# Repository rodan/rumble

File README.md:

# rumble

sandbox for geophone amplifiers

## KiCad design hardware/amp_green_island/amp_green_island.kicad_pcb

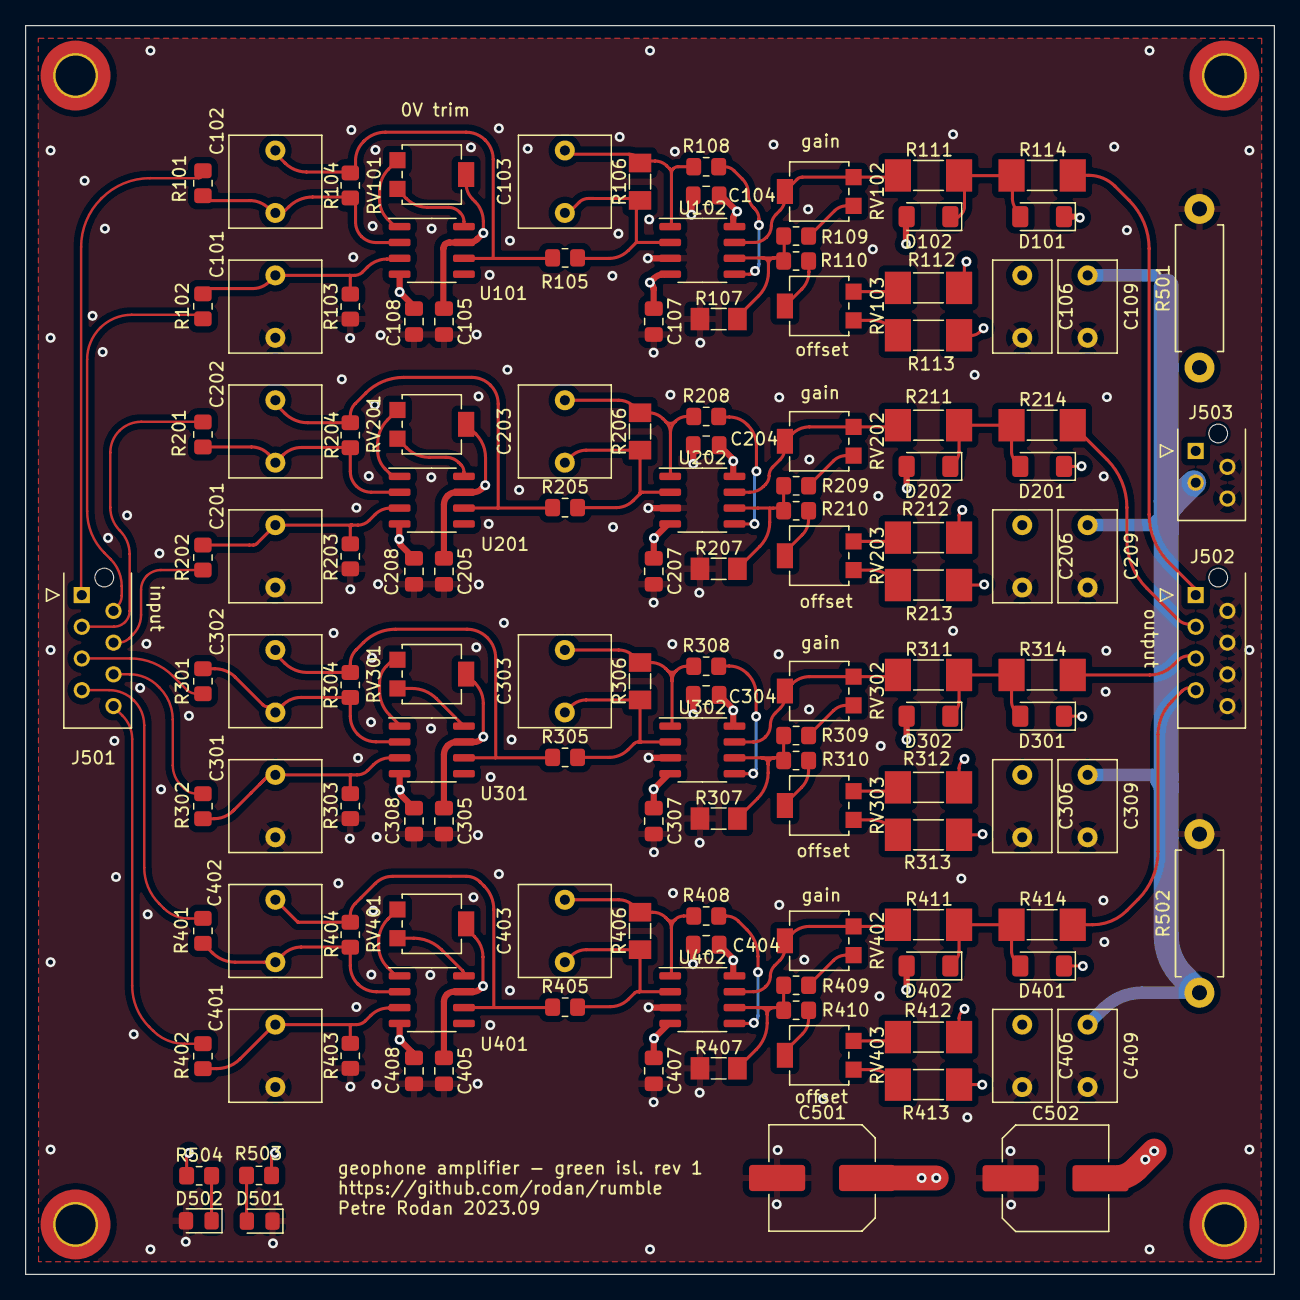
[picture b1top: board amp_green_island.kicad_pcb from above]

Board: 4 copper layers, 100.0 x 100.0 mm, 131 parts (0 on the bottom side), 77 nets.

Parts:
C101, C102, C103, C201, C202, C203, C301, C302, C303, C401, C402, C403: 1u; C_Rect_L7.2mm_W7.2mm_P5.00mm_FKS2_FKP2_MKS2_MKP2
C104, C105, C107, C108, C204, C205, C207, C208, C304, C305, C307, C308, C404, C405, C407, C408: 100n; C_0805_2012Metric_Pad1.18x1.45mm_HandSolder
C106, C109, C206, C209, C306, C309, C406, C409: 100n; C_Rect_L7.2mm_W4.5mm_P5.00mm_FKS2_FKP2_MKS2_MKP2
C501, C502: 220u; C_Elec_8x10.2
D101, D102, D201, D202, D301, D302, D401, D402: LL4148; D_MiniMELF
D501, D502: LED; LED_0805_2012Metric_Pad1.15x1.40mm_HandSolder
J501: input; TE_Micro-MaTch_215079-8_2x04_P1.27mm_Vertical
J502: output; TE_Micro-MaTch_215079-8_2x04_P1.27mm_Vertical
J503: Conn_01x04_Pin; TE_Micro-MaTch_215079-4_2x02_P1.27mm_Vertical
R101, R102, R201, R202, R301, R302, R401, R402: 10k; R_0805_2012Metric_Pad1.20x1.40mm_HandSolder
R103, R104, R203, R204, R303, R304, R403, R404, R503, R504: 100k; R_0805_2012Metric_Pad1.20x1.40mm_HandSolder
R105, R108, R205, R208, R305, R308, R405, R408: 1k; R_0805_2012Metric_Pad1.20x1.40mm_HandSolder
R106, R206, R306, R406: 200k; R_MiniMELF_MMA-0204
R107, R207, R307, R407: 3k3; R_MiniMELF_MMA-0204
R109, R209, R309, R409: 5k6; R_0805_2012Metric_Pad1.20x1.40mm_HandSolder
R110, R210, R310, R410: 82k; R_0805_2012Metric_Pad1.20x1.40mm_HandSolder
R111, R114, R211, R214, R311, R314, R411, R414: 470; R_MELF_MMB-0207
R112, R113, R212, R213, R312, R313, R412, R413: 33k; R_MELF_MMB-0207
R501, R502: 100; R_Axial_DIN0411_L9.9mm_D3.6mm_P12.70mm_Horizontal
RV101, RV201, RV301, RV401: 10k; Potentiometer_Bourns_3314G_Vertical
RV102, RV202, RV302, RV402: 50k; Potentiometer_Bourns_3314G_Vertical
RV103, RV203, RV303, RV403: 5k; Potentiometer_Bourns_3314G_Vertical
U101, U201, U301, U401: OP27; SO-8_3.9x4.9mm_P1.27mm
U102, U202, U302, U402: TL072; SO-8_3.9x4.9mm_P1.27mm

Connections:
+12V: C104.1, C105.1, C106.1, C204.1, C205.1, C206.1, C304.1, C305.1, C306.1, C404.1, C405.1, C406.1, C501.1, D101.1 (K), D201.1 (K), D301.1 (K), D401.1 (K), J503.1, R112.1, R212.1, R312.1, R412.1, R501.1, R503.1, RV101.2, RV201.2, RV301.2, RV401.2, U101.7 (V+), U102.8 (V+), U201.7 (V+), U202.8 (V+), U301.7 (V+), U302.8 (V+), U401.7 (V+), U402.8 (V+)
-12V: C107.1, C108.1, C109.1, C207.1, C208.1, C209.1, C307.1, C308.1, C309.1, C407.1, C408.1, C409.1, C502.2, D102.2 (A), D202.2 (A), D302.2 (A), D402.2 (A), J503.3, R113.2, R213.2, R313.2, R413.2, R502.1, R504.1, U101.4 (V-), U102.4 (V-), U201.4 (V-), U202.4 (V-), U301.4 (V-), U302.4 (V-), U401.4 (V-), U402.4 (V-)
GND: C101.1, C104.2, C105.2, C106.2, C107.2, C108.2, C109.2, C201.1, C204.2, C205.2, C206.2, C207.2, C208.2, C209.2, C301.1, C304.2, C305.2, C306.2, C307.2, C308.2, C309.2, C401.1, C404.2, C405.2, C406.2, C407.2, C408.2, C409.2, C501.2, C502.1, D501.1 (K), D502.2 (A), J502.2, J502.4, J502.6, J502.8, J503.2, J503.4, R103.1, R107.1, R203.1, R207.1, R303.1, R307.1, R403.1, R407.1, R501.2, R502.2, U102.3 (+), U202.3 (+), U302.3 (+), U402.3 (+)
unnamed: C102.2, R104.1, R105.1, U101.6
unnamed: C103.2, R106.2, R108.1, U102.1
unnamed: C202.2, R204.1, R205.1, U201.6
unnamed: C203.2, R206.2, R208.1, U202.1
unnamed: C302.2, R304.1, R305.1, U301.6
unnamed: C303.2, R306.2, R308.1, U302.1
unnamed: C402.2, R404.1, R405.1, U401.6
unnamed: C403.2, R406.2, R408.1, U402.1
unnamed: D101.2 (A), D102.1 (K), R111.2, R114.1
unnamed: D201.2 (A), D202.1 (K), R211.2, R214.1
unnamed: D301.2 (A), D302.1 (K), R311.2, R314.1
unnamed: D401.2 (A), D402.1 (K), R411.2, R414.1
unnamed: D501.2 (A), R503.2
unnamed: D502.1 (K), R504.2
unnamed: R109.2, RV102.1
unnamed: R110.2, RV103.2
unnamed: R111.1, RV102.2, RV102.3, U102.7
unnamed: R112.2, RV103.3
unnamed: R113.1, RV103.1
unnamed: R209.2, RV202.1
unnamed: R210.2, RV203.2
unnamed: R211.1, RV202.2, RV202.3, U202.7
unnamed: R212.2, RV203.3
unnamed: R213.1, RV203.1
unnamed: R309.2, RV302.1
unnamed: R310.2, RV303.2
unnamed: R311.1, RV302.2, RV302.3, U302.7
unnamed: R312.2, RV303.3
unnamed: R313.1, RV303.1
unnamed: R409.2, RV402.1
unnamed: R410.2, RV403.2
unnamed: R411.1, RV402.2, RV402.3, U402.7
unnamed: R412.2, RV403.3
unnamed: R413.1, RV403.1
unnamed: C101.2, R102.2, R103.2, U101.3 (+)
unnamed: C102.1, R101.2, R104.2, U101.2 (-)
unnamed: RV101.1, U101.1 (TRIM1)
unnamed: RV101.3, U101.8 (TRIM8)
unnamed: C103.1, R105.2, R106.1, U102.2 (-)
unnamed: R108.2, U102.5 (+)
unnamed: R107.2, R109.1, R110.1, U102.6 (-)
unnamed: C201.2, R202.2, R203.2, U201.3 (+)
unnamed: C202.1, R201.2, R204.2, U201.2 (-)
unnamed: RV201.1, U201.1 (TRIM1)
unnamed: RV201.3, U201.8 (TRIM8)
unnamed: C203.1, R205.2, R206.1, U202.2 (-)
unnamed: R208.2, U202.5 (+)
unnamed: R207.2, R209.1, R210.1, U202.6 (-)
unnamed: C301.2, R302.2, R303.2, U301.3 (+)
unnamed: C302.1, R301.2, R304.2, U301.2 (-)
unnamed: RV301.1, U301.1 (TRIM1)
unnamed: RV301.3, U301.8 (TRIM8)
unnamed: C303.1, R305.2, R306.1, U302.2 (-)
unnamed: R308.2, U302.5 (+)
unnamed: R307.2, R309.1, R310.1, U302.6 (-)
unnamed: C401.2, R402.2, R403.2, U401.3 (+)
unnamed: C402.1, R401.2, R404.2, U401.2 (-)
unnamed: RV401.1, U401.1 (TRIM1)
unnamed: RV401.3, U401.8 (TRIM8)
unnamed: C403.1, R405.2, R406.1, U402.2 (-)
unnamed: R408.2, U402.5 (+)
unnamed: R407.2, R409.1, R410.1, U402.6 (-)
in1_+: J501.2, R102.1
in1_-: J501.1, R101.1
in2_+: J501.4, R202.1
in2_-: J501.3, R201.1
in3_+: J501.6, R302.1
in3_-: J501.5, R301.1
in4_+: J501.8, R402.1
in4_-: J501.7, R401.1
out1: J502.1, R114.2
out2: J502.3, R214.2
out3: J502.5, R314.2
out4: J502.7, R414.2

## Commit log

2023-09-10 add lt1677-based preamp
2023-09-10 add amp_anubi schematic
2023-09-11 add amp_green_island schematic
2023-09-11 amp_green_island: add all 4 channels to schematic
2023-09-12 green_island: pcb routing done
2023-09-13 amp_green_island: pcb verified
2023-09-20 pcb sent to production
2023-11-01 add ltspice simulation
2023-11-01 better frequency response
2023-11-02 filters generated by TI's online filter design tool
2024-04-18 latest
